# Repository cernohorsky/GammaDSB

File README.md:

# Gamma DSB Transceiver

This only smd version of D4D DSB Transceiver Kit for Digital Mode http://crkits.com/

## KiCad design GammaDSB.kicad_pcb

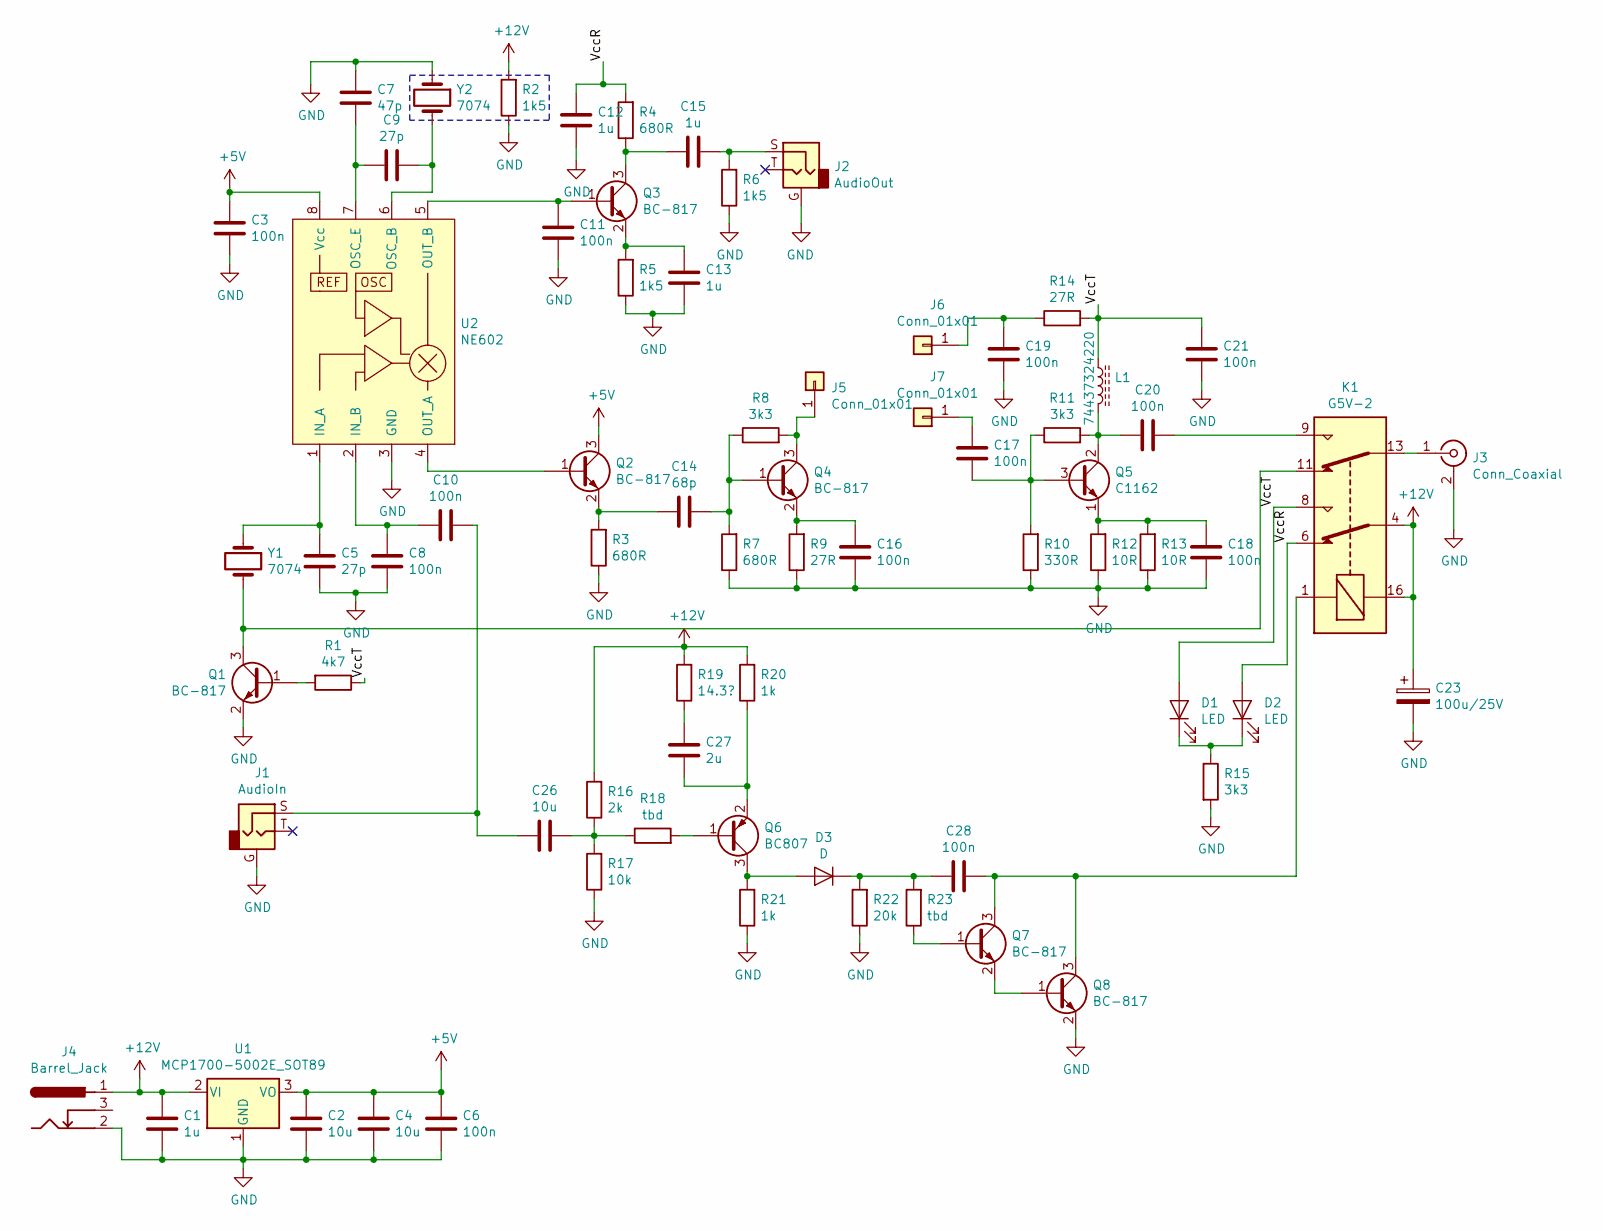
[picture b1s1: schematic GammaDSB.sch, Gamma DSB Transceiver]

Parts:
C1, C12, C13, C15: 1u; C_0805_2012Metric
C2, C4, C26: 10u; C_0805_2012Metric
C3, C6, C8, C10, C11, C16, C17, C18, C19, C20, C21, C28: 100n; C_0603_1608Metric
C5, C9: 27p; C_0603_1608Metric
C7: 47p; C_0603_1608Metric
C14: 68p; C_0603_1608Metric
C23: 100u/25V; CP_Elec_10x10.5
C27: 2u; C_0805_2012Metric
D1, D2: LED; LED_1206_3216Metric
D3: D; D_SOD-123
J1: AudioIn; Jack_3.5mm_CUI_SJ1-3533NG_Horizontal
J2: AudioOut; Jack_3.5mm_CUI_SJ1-3533NG_Horizontal
J3: Conn_Coaxial; SMA_Amphenol_132289_EdgeMount
J4: Barrel_Jack; BarrelJack_Horizontal
J5, J6, J7: Conn_01x01; SolderWirePad_1x01_Drill0.8mm
K1: G5V-2; Relay_DPDT_Omron_G5V-2
L1: 74437324220; L_Wuerth_HCI-5040
Q1, Q2, Q3, Q4, Q7, Q8: BC-817; SOT-23
Q5: C1162; TO-126-3_Horizontal_TabUp
Q6: BC807; SOT-23
R1: 4k7; R_0603_1608Metric
R2: 1k5; R_Axial_DIN0207_L6.3mm_D2.5mm_P10.16mm_Horizontal
R3, R4, R7: 680R; R_0603_1608Metric
R5, R6: 1k5; R_0603_1608Metric
R8, R11, R15: 3k3; R_0603_1608Metric
R9, R14: 27R; R_0603_1608Metric
R10: 330R; R_0603_1608Metric
R12, R13: 10R; R_0603_1608Metric
R16: 2k; R_0603_1608Metric
R17: 10k; R_0603_1608Metric
R18, R23: tbd; R_0603_1608Metric
R19: 14.3?; R_0603_1608Metric
R20, R21: 1k; R_0603_1608Metric
R22: 20k; R_0603_1608Metric
U1: MCP1700-5002E_SOT89; SOT-89-3
U2: NE602; SO-8_5.3x6.2mm_P1.27mm
Y1, Y2: 7074; Crystal_SMD_HC49-SD

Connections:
+5V: C2.1, C3.1, C4.1, C6.1, Q2.3 (C), U1.3 (VO), U2.8 (Vcc)
+12V: C1.2, C23.1, J4.1, K1.4, K1.16, R2.2, R16.2, R19.2, R20.2, U1.2 (VI)
/VccR: C12.2, D2.2 (A), K1.6, R4.2
/VccT: C21.2, D1.2 (A), K1.8, L1.1, R1.1, R14.2
GND: C1.1, C2.2, C3.2, C4.2, C5.2, C6.2, C7.2, C8.2, C11.1, C12.1, C13.1, C16.1, C18.1, C19.1, C21.1, C23.2, J1.G, J2.G, J3.2 (Ext), J4.2, Q1.2 (E), Q8.2 (E), R2.1, R3.1, R5.1, R6.1, R7.1, R9.1, R10.1, R12.1, R13.1, R15.2, R17.1, R21.1, R22.1, U1.1 (GND), U2.3 (GND), Y2.1
unnamed: C5.1, U2.1 (IN_A), Y1.1
unnamed: C7.1, C9.2, U2.7 (OSC_E)
unnamed: C9.1, U2.6 (OSC_B), Y2.2
unnamed: C10.1, C26.2, J1.S
unnamed: C8.1, C10.2, U2.2 (IN_B)
unnamed: C11.2, Q3.1 (B), U2.5 (OUT_B)
unnamed: C13.2, Q3.2 (E), R5.2
unnamed: C14.1, Q4.1 (B), R7.2, R8.1
unnamed: C14.2, Q2.2 (E), R3.2
unnamed: C15.1, Q3.3 (C), R4.1
unnamed: C15.2, J2.S, R6.2
unnamed: C16.2, Q4.2 (E), R9.2
unnamed: C17.1, Q5.3 (B), R10.2, R11.1
unnamed: C17.2, J7.1
unnamed: C18.2, Q5.1 (E), R12.2, R13.2
unnamed: C19.2, J6.1, R14.1
unnamed: C20.1, L1.2, Q5.2 (C), R11.2
unnamed: C20.2, K1.9
unnamed: C26.1, R16.1, R17.2, R18.1
unnamed: C27.1, Q6.2 (E), R20.1
unnamed: C27.2, R19.1
unnamed: C28.1, K1.1, Q7.3 (C), Q8.3 (C)
unnamed: C28.2, D3.1 (K), R22.2, R23.2
unnamed: D1.1 (K), D2.1 (K), R15.1
unnamed: D3.2 (A), Q6.3 (C), R21.2
unnamed: J3.1 (In), K1.13
unnamed: J5.1, Q4.3 (C), R8.2
unnamed: K1.11, Q1.3 (C), Y1.2
unnamed: Q1.1 (B), R1.2
unnamed: Q2.1 (B), U2.4 (OUT_A)
unnamed: Q6.1 (B), R18.2
unnamed: Q7.1 (B), R23.1
unnamed: Q7.2 (E), Q8.1 (B)

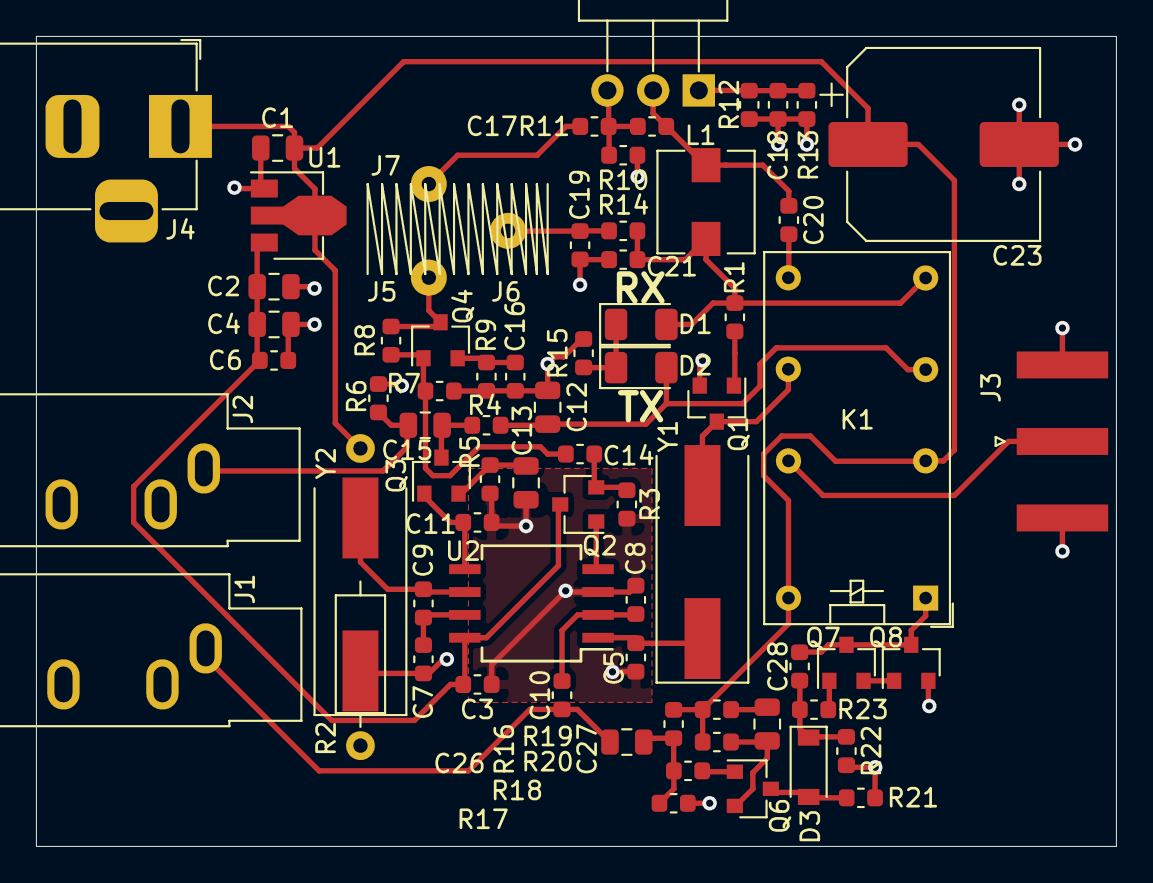
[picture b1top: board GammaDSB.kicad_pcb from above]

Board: 2 copper layers, 60.0 x 45.0 mm, 72 parts (0 on the bottom side), 38 nets.

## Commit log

2021-01-26 Version 0.1
2021-01-27 Small improvements.
2021-02-19 Changed L1 and T1 footprints
2021-02-19 Changed layout, removed filter, smaller PCB size.
